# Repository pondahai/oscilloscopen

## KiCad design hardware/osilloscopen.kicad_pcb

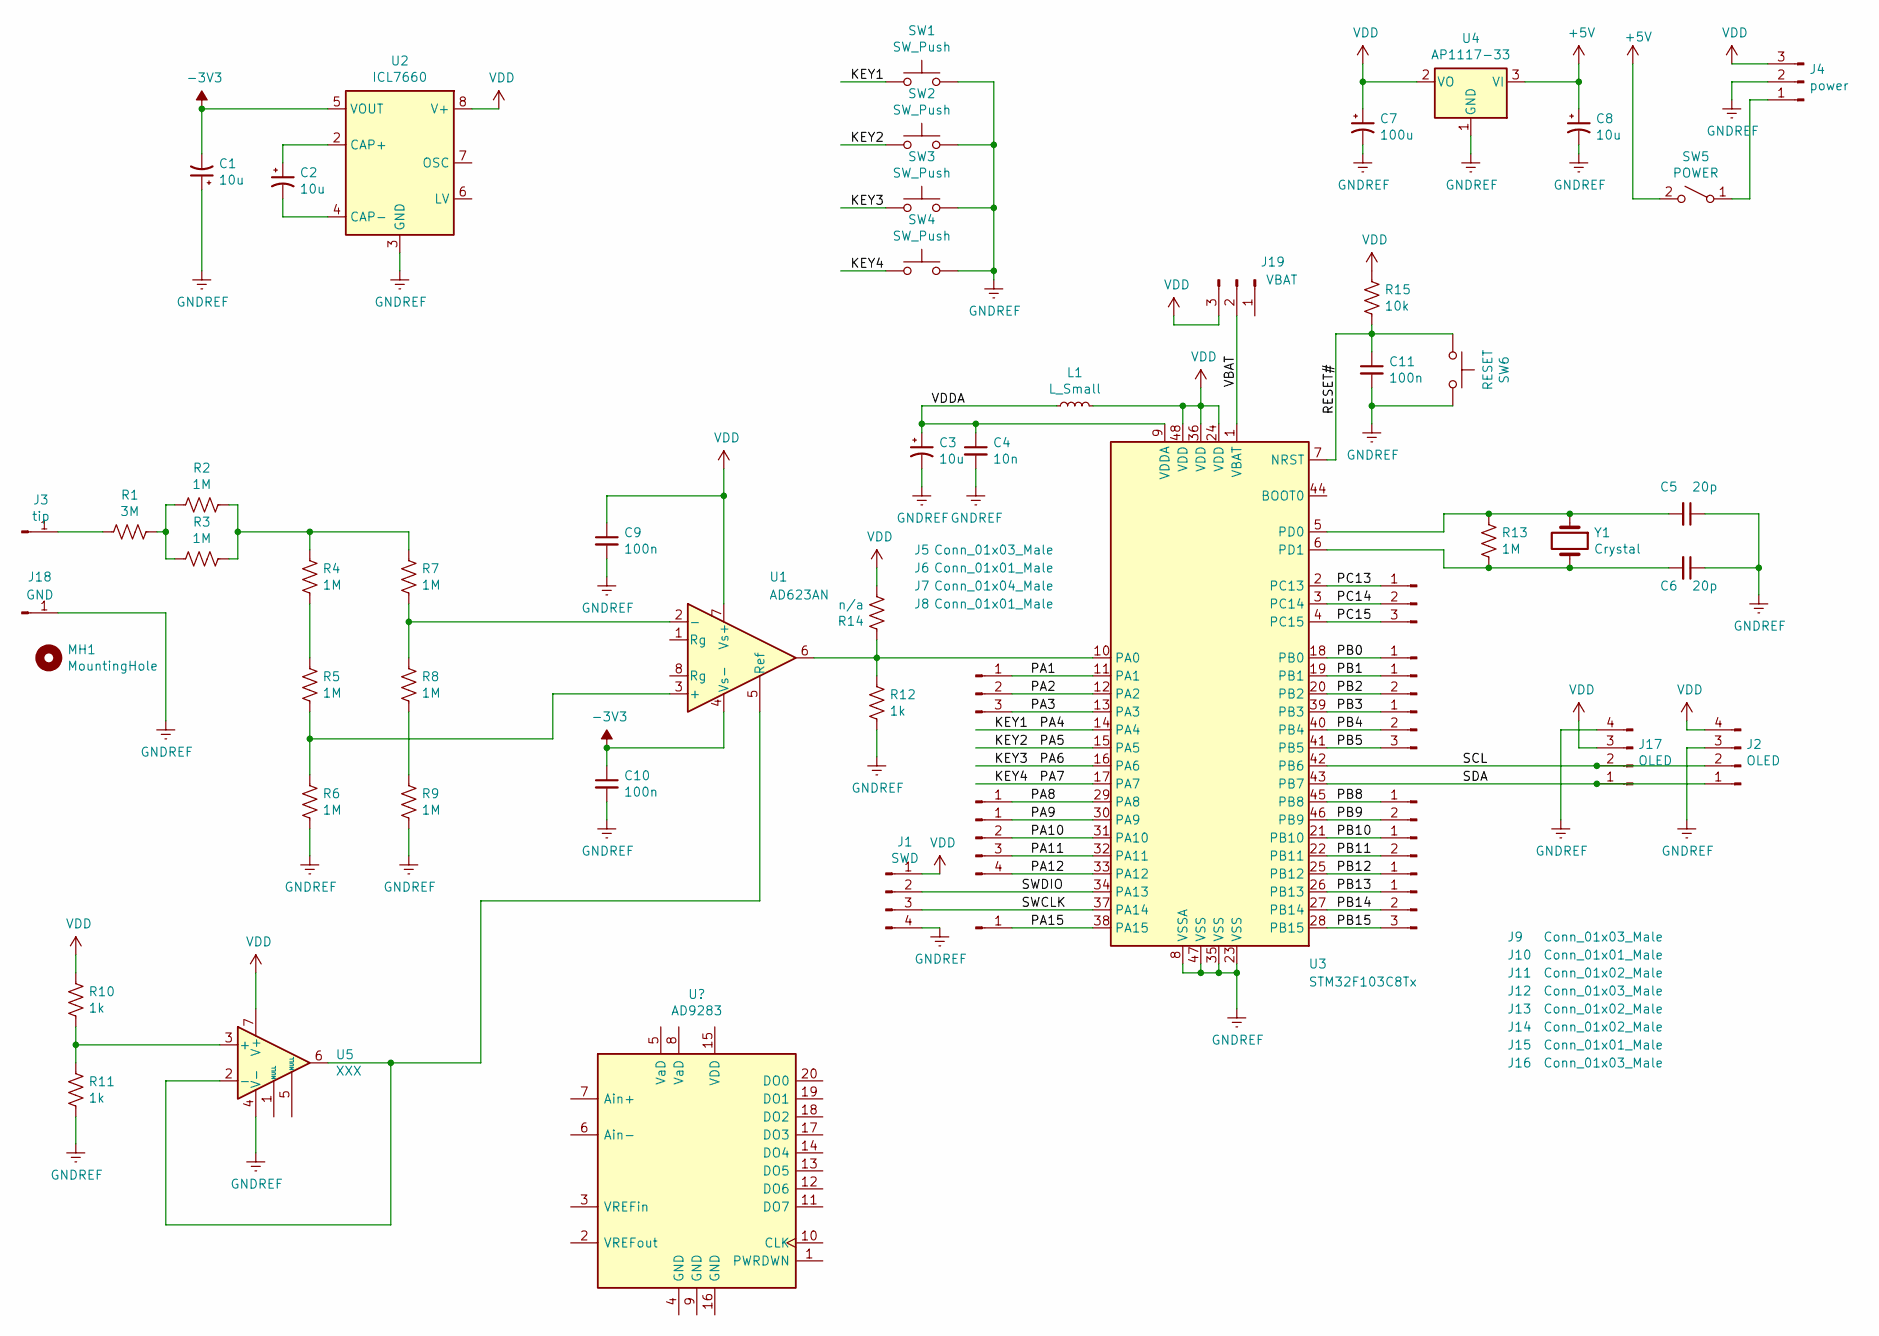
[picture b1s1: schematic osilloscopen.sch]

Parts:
C1, C2, C3, C8: 10u; CP_Radial_D6.3mm_P2.50mm
C4: 10n; C_Disc_D4.7mm_W2.5mm_P5.00mm
C5, C6: 20p; C_Disc_D4.7mm_W2.5mm_P5.00mm
C7: 100u; CP_Radial_D6.3mm_P2.50mm
C9, C10, C11: 100n; C_Disc_D6.0mm_W2.5mm_P5.00mm
J1: SWD; PinHeader_1x04_P2.54mm_Vertical
J2, J17: OLED; PinHeader_1x04_P2.54mm_Vertical
J3: tip; PinHeader_1x01_P2.54mm_Vertical
J4: power; PinHeader_1x03_P2.54mm_Vertical
J5, J9, J12, J16: Conn_01x03_Male; PinHeader_1x03_P2.54mm_Vertical
J6, J8, J10, J15: Conn_01x01_Male; PinHeader_1x01_P2.54mm_Vertical
J7: Conn_01x04_Male; PinHeader_1x04_P2.54mm_Vertical
J11, J13, J14: Conn_01x02_Male; PinHeader_1x02_P2.54mm_Vertical
J18: GND; SolderWirePad_1x01_Drill1.5mm
J19: VBAT; PinHeader_1x03_P2.54mm_Vertical
L1: L_Small; L_Axial_L5.3mm_D2.2mm_P7.62mm_Horizontal_Vishay_IM-1
MH1: MountingHole; MountingHole_3.5mm
R1: 3M; R_Axial_DIN0207_L6.3mm_D2.5mm_P10.16mm_Horizontal
R2, R3, R4, R5, R6, R7, R8, R9, R13: 1M; R_Axial_DIN0207_L6.3mm_D2.5mm_P10.16mm_Horizontal
R10, R11, R12: 1k; R_Axial_DIN0207_L6.3mm_D2.5mm_P10.16mm_Horizontal
R14: n/a; R_Axial_DIN0207_L6.3mm_D2.5mm_P10.16mm_Horizontal
R15: 10k; R_Axial_DIN0207_L6.3mm_D2.5mm_P10.16mm_Horizontal
SW1, SW2, SW3, SW4: SW_Push; SW_PUSH_6mm_H5mm
SW5: POWER; SW_CuK_OS102011MA1QN1_SPDT_Angled
SW6: RESET; SW_PUSH_6mm_H5mm
U1: AD623AN; DIP-8_W7.62mm_LongPads
U2: ICL7660; DIP-8_W7.62mm_LongPads
U3: STM32F103C8Tx; LQFP-48_7x7mm_P0.5mm
U4: AP1117-33; SOT-223-3_TabPin2
U5: XXX; DIP-8_W7.62mm_LongPads
Y1: Crystal; Crystal_HC49-4H_Vertical

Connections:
+5V: C8.1, SW5.2 (B), U4.3 (VI)
-3V3: C1.2, C10.1, U1.4 (Vs-), U2.5 (VOUT)
/KEY1: SW1.1, U3.14 (PA4)
/KEY2: SW2.1, U3.15 (PA5)
/KEY3: SW3.1, U3.16 (PA6)
/KEY4: SW4.1, U3.17 (PA7)
/PA1: J5.1, U3.11 (PA1)
/PA2: J5.2, U3.12 (PA2)
/PA3: J5.3, U3.13 (PA3)
/PA8: J6.1, U3.29 (PA8)
/PA9: J7.1, U3.30 (PA9)
/PA10: J7.2, U3.31 (PA10)
/PA11: J7.3, U3.32 (PA11)
/PA12: J7.4, U3.33 (PA12)
/PA15: J8.1, U3.38 (PA15)
/PB0: J10.1, U3.18 (PB0)
/PB1: J11.1, U3.19 (PB1)
/PB2: J11.2, U3.20 (PB2)
/PB3: J12.1, U3.39 (PB3)
/PB4: J12.2, U3.40 (PB4)
/PB5: J12.3, U3.41 (PB5)
/PB8: J13.1, U3.45 (PB8)
/PB9: J13.2, U3.46 (PB9)
/PB10: J14.1, U3.21 (PB10)
/PB11: J14.2, U3.22 (PB11)
/PB12: J15.1, U3.25 (PB12)
/PB13: J16.1, U3.26 (PB13)
/PB14: J16.2, U3.27 (PB14)
/PB15: J16.3, U3.28 (PB15)
/PC13: J9.1, U3.2 (PC13)
/PC14: J9.2, U3.3 (PC14)
/PC15: J9.3, U3.4 (PC15)
/RESET#: C11.1, R15.2, SW6.1, U3.7 (NRST)
/SCL: J2.2, J17.2, U3.42 (PB6)
/SDA: J2.1, J17.1, U3.43 (PB7)
/SWCLK: J1.3, U3.37 (PA14)
/SWDIO: J1.2, U3.34 (PA13)
/VBAT: J19.2, U3.1 (VBAT)
/VDDA: C3.1, C4.1, L1.1, U3.9 (VDDA)
GNDREF: C1.1, C3.2, C4.2, C5.1, C6.1, C7.2, C8.2, C9.2, C10.2, C11.2, J1.4, J2.3, J4.2, J17.4, J18.1, R6.1, R9.1, R11.1, R12.1, SW1.2, SW2.2, SW3.2, SW4.2, SW6.2, U2.3 (GND), U3.8 (VSSA), U3.23 (VSS), U3.35 (VSS), U3.47 (VSS), U4.1 (GND), U5.4 (V-)
unnamed: C2.1, U2.2 (CAP+)
unnamed: C2.2, U2.4 (CAP-)
unnamed: C5.2, R13.1, U3.5 (PD0), Y1.1
unnamed: C6.2, R13.2, U3.6 (PD1), Y1.2
unnamed: J3.1, R1.2
unnamed: J4.1, SW5.1 (A)
unnamed: R1.1, R2.2, R3.2
unnamed: R2.1, R3.1, R4.2, R7.2
unnamed: R4.1, R5.2
unnamed: R5.1, R6.2, U1.3 (+)
unnamed: R7.1, R8.2, U1.2 (-)
unnamed: R8.1, R9.2
unnamed: R10.1, R11.2, U5.3 (+)
unnamed: R12.2, R14.2, U1.6, U3.10 (PA0)
unnamed: U1.5 (Ref), U5.2 (-), U5.6
VDD: C7.1, C9.1, J1.1, J2.4, J4.3, J17.3, J19.3, L1.2, R10.2, R14.1, R15.1, U1.7 (Vs+), U2.8 (V+), U3.24 (VDD), U3.36 (VDD), U3.48 (VDD), U4.2 (VO), U5.7 (V+)

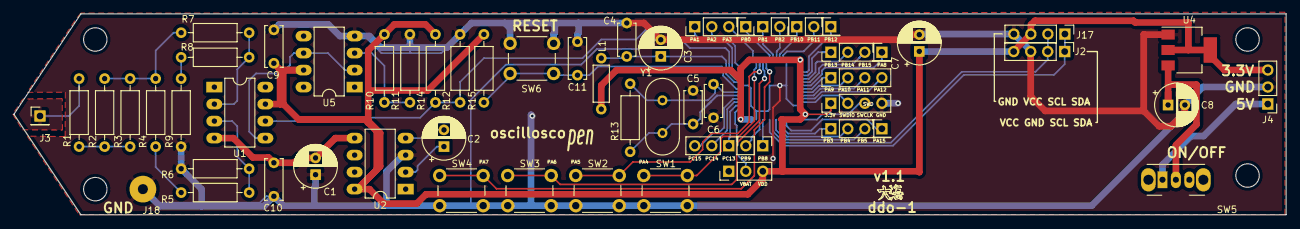
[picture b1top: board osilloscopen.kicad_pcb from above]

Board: 2 copper layers, 190.0 x 30.0 mm, 62 parts (1 on the bottom side), 56 nets.

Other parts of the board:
MH2, MH3, MH4: MountingHole; MountingHole_3.5mm

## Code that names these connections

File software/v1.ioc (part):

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Mcu.Name=STM32F103C(8-B)Tx
Mcu.Package=LQFP48
Mcu.UserName=STM32F103C8Tx
PA0-WKUP.Signal=ADCx_IN0
PA13.Mode=Serial_Wire
PA13.Signal=SYS_JTMS-SWDIO
PA14.Mode=Serial_Wire
PA14.Signal=SYS_JTCK-SWCLK
PA4.GPIOParameters=GPIO_PuPd
PA4.GPIO_PuPd=GPIO_PULLUP
PA4.Signal=GPIO_Input
PA5.GPIOParameters=GPIO_PuPd
PA5.GPIO_PuPd=GPIO_PULLUP
PA5.Signal=GPIO_Input
PA6.GPIOParameters=GPIO_PuPd
PA6.GPIO_PuPd=GPIO_PULLUP
PA6.Signal=GPIO_Input
PA7.GPIOParameters=GPIO_PuPd
PA7.GPIO_PuPd=GPIO_PULLUP
PA7.Signal=GPIO_Input
PB6.Mode=I2C
PB6.Signal=I2C1_SCL
PB7.Mode=I2C
PB7.Signal=I2C1_SDA
PB8.GPIOParameters=GPIO_Speed,PinState
PB8.GPIO_Speed=GPIO_SPEED_FREQ_HIGH
PB8.PinState=GPIO_PIN_RESET
PB8.Signal=GPIO_Output
PD0-OSC_IN.Mode=HSE-External-Oscillator
PD0-OSC_IN.Signal=RCC_OSC_IN
PD1-OSC_OUT.Mode=HSE-External-Oscillator
PD1-OSC_OUT.Signal=RCC_OSC_OUT
RCC.SYSCLKFreq_VALUE=56000000
RCC.SYSCLKSource=RCC_SYSCLKSOURCE_PLLCLK
board=custom

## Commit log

2019-03-27 Rename readme to readme.md
